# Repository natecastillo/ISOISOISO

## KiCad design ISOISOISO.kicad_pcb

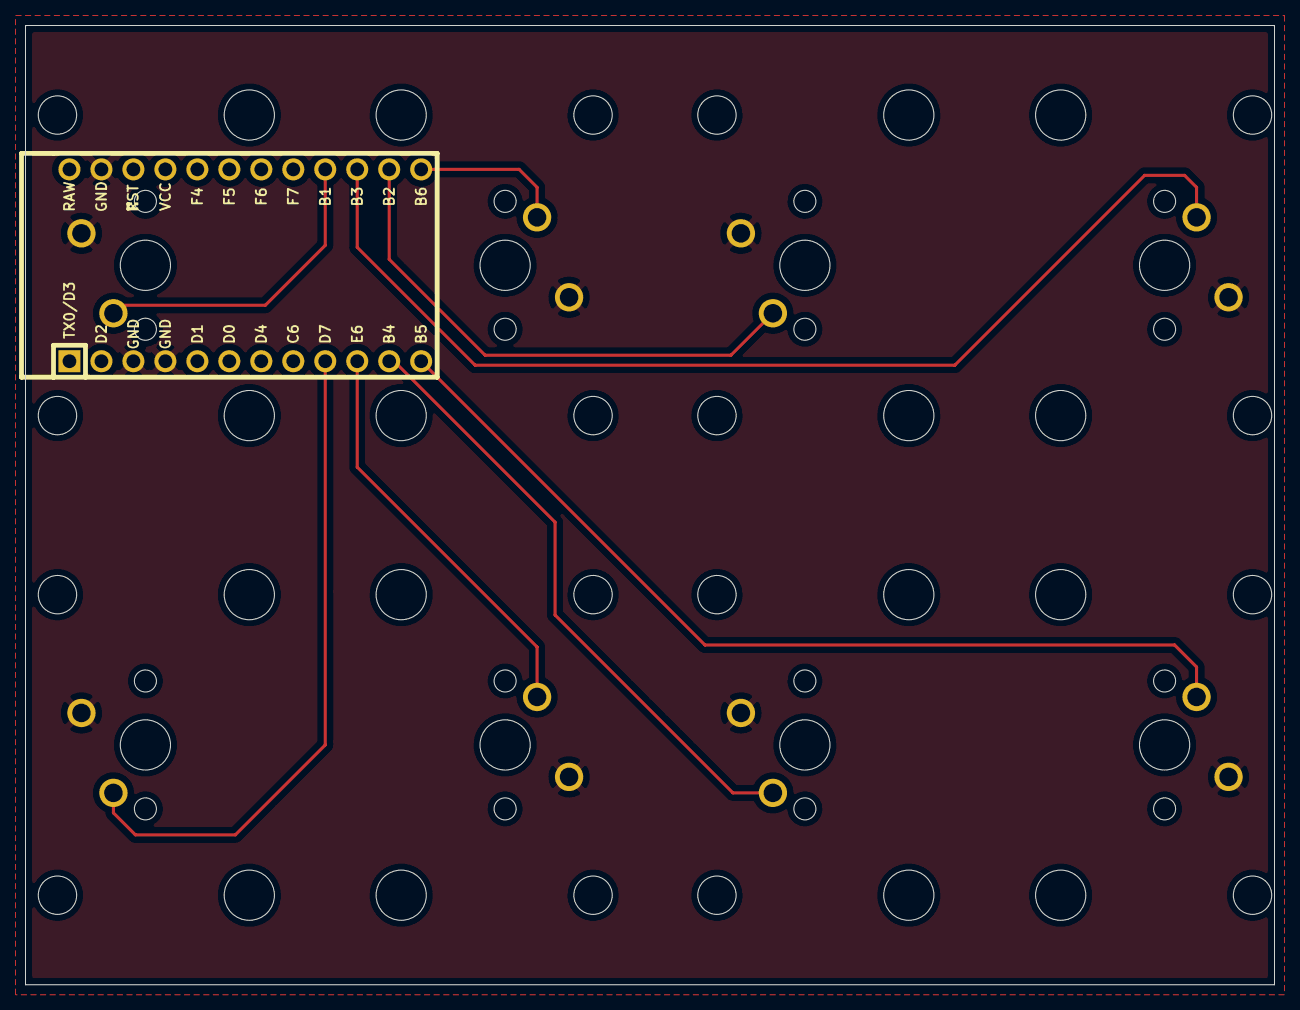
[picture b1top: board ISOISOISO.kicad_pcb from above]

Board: 2 copper layers, 99.2 x 76.2 mm, 9 parts (0 on the bottom side), 9 nets.

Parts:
MX1, MX2, MX3, MX4, MX5, MX6, MX7, MX8: MX-NoLED; MXOnly-ISO-ROTATED-ReversedStabilizers-NoLED
U1: ProMicro; ArduinoProMicro

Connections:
GND: MX1.2, MX2.2, MX3.2, MX4.2, MX5.2, MX6.2, MX7.2, MX8.2, U1.3, U1.4, U1.23
SW1: MX1.1, U1.16
SW2: MX3.1, U1.13
SW3: MX5.1, U1.14
SW4: MX7.1, U1.15
SW5: MX2.1, U1.9
SW6: MX4.1, U1.10
SW7: MX6.1, U1.11
SW8: MX8.1, U1.12

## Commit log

2021-04-18 Upload files
